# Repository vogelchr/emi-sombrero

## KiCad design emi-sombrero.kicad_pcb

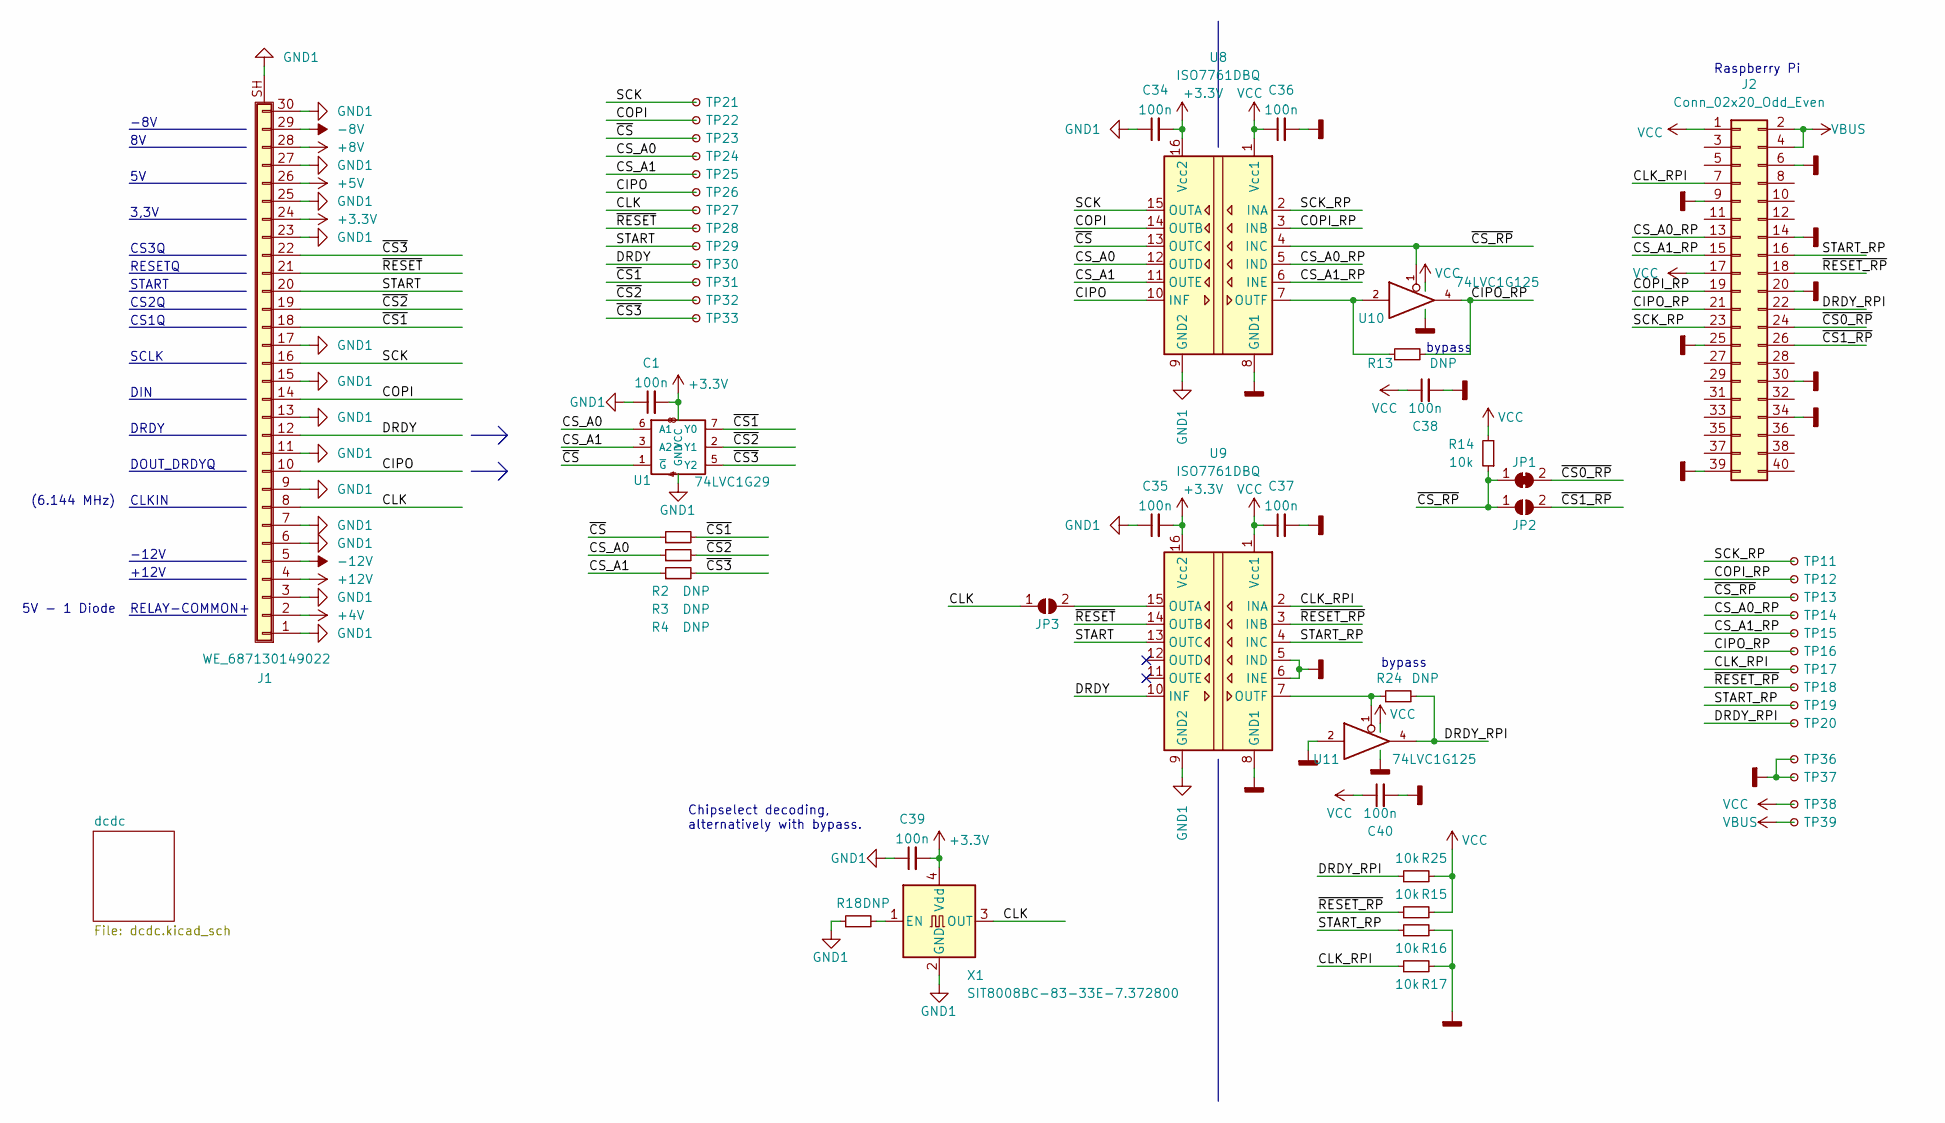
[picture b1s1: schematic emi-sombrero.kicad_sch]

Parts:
C1, C34, C35, C36, C37, C38, C39, C40: 100n; C_0603_1608Metric
J1: WE_687130149022; Hirose_FH12-30S-0.5SH_1x30-1MP_P0.50mm_Horizontal
J2: Conn_02x20_Odd_Even; PinHeader_2x20_P2.54mm_Vertical
JP1: SolderJumper_2_Bridged; SolderJumper-2_P1.3mm_Bridged_Pad1.0x1.5mm
JP2, JP3: SolderJumper_2_Open; SolderJumper-2_P1.3mm_Open_Pad1.0x1.5mm
R2, R3, R4, R13, R18, R24: DNP; R_0603_1608Metric
R14, R15, R16, R17, R25: 10k; R_0603_1608Metric
TP11, TP12, TP13, TP14, TP15, TP16, TP17, TP18, TP19, TP20, TP21, TP22, TP23, TP24, TP25, TP26, TP27, TP28, TP29, TP30, TP31, TP32, TP33, TP36, TP37, TP38, TP39: TestPoint_Small; TestPoint_Pad_1.5x1.5mm
U1: 74LVC1G29; SSOP-8_2.95x2.8mm_P0.65mm
U8, U9: ISO7761DBQ; SSOP-16_3.9x4.9mm_P0.635mm
U10, U11: 74LVC1G125; SOT-23-5
X1: SIT8008BC-83-33E-7.372800; Oscillator_SMD_TXC_7C-4Pin_5.0x3.2mm

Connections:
+3V3: C1.2, C34.2, C35.2, C39.2, J1.24, U1.8 (VCC), U8.16 (Vcc2), U9.16 (Vcc2), X1.4 (Vdd); also elsewhere on the board
+4V: J1.2; also elsewhere on the board
+5V: J1.26; also elsewhere on the board
+8V: J1.28; also elsewhere on the board
+12V: J1.4; also elsewhere on the board
-8V: J1.29; also elsewhere on the board
-12V: J1.5; also elsewhere on the board
/CIPO: J1.10, TP26.1, U8.10 (INF)
/CIPO_RP: J2.21, R13.2, TP16.1, U10.4
/CLK: J1.8, JP3.1 (A), TP27.1, X1.3 (OUT)
/CLK_RPI: J2.7, R17.1, TP17.1, U9.2 (INA)
/COPI: J1.14, TP22.1, U8.14 (OUTB)
/COPI_RP: J2.19, TP12.1, U8.3 (INB)
/CS_A0: R3.1, TP24.1, U1.6 (A1), U8.12 (OUTD)
/CS_A0_RP: J2.13, TP14.1, U8.5 (IND)
/CS_A1: R4.1, TP25.1, U1.3 (A2), U8.11 (OUTE)
/CS_A1_RP: J2.15, TP15.1, U8.6 (INE)
/DRDY: J1.12, TP30.1, U9.10 (INF)
/DRDY_RPI: J2.22, R24.2, R25.1, TP20.1, U11.4
/SCK: J1.16, TP21.1, U8.15 (OUTA)
/SCK_RP: J2.23, TP11.1, U8.2 (INA)
/START: J1.20, TP29.1, U9.13 (OUTC)
/START_RP: J2.16, R16.1, TP19.1, U9.4 (INC)
/~CS0_RP: J2.24, JP1.2 (B)
/~CS1_RP: J2.26, JP2.2 (B)
/~CS1: J1.18, R2.2, TP31.1, U1.7 (Y0)
/~CS2: J1.19, R3.2, TP32.1, U1.2 (Y1)
/~CS3: J1.22, R4.2, TP33.1, U1.5 (Y2)
/~CS_RP: JP1.1 (A), JP2.1 (A), R14.1, TP13.1, U8.4 (INC), U10.1
/~CS: R2.1, TP23.1, U1.1 (~G), U8.13 (OUTC)
/~RESET_RP: J2.18, R15.1, TP18.1, U9.3 (INB)
/~RESET: J1.21, TP28.1, U9.14 (OUTB)
GND: C36.2, C37.2, C38.2, C40.2, J2.6, J2.9, J2.14, J2.20, J2.25, J2.30, J2.34, J2.39, R16.2, R17.2, TP36.1, TP37.1, U8.8 (GND1), U9.5 (IND), U9.6 (INE), U9.8 (GND1), U10.3 (GND), U11.2, U11.3 (GND); also elsewhere on the board
GND1: C1.1, C34.1, C35.1, C39.1, J1.1, J1.3, J1.6, J1.7, J1.9, J1.11, J1.13, J1.15, J1.17, J1.23, J1.25, J1.27, J1.30, J1.SH (Shield), R18.1, U1.4 (GND), U8.9 (GND2), U9.9 (GND2), X1.2 (GND); also elsewhere on the board
unnamed: JP3.2 (B), U9.15 (OUTA)
unnamed: R13.1, U8.7 (OUTF), U10.2
unnamed: R18.2, X1.1 (EN)
unnamed: R24.1, U9.7 (OUTF), U11.1
VBUS: J2.2, J2.4, TP39.1; also elsewhere on the board
VCC: C36.1, C37.1, C38.1, C40.1, J2.1, J2.17, R14.2, R15.2, R25.2, TP38.1, U8.1 (Vcc1), U9.1 (Vcc1), U10.5 (VCC), U11.5 (VCC); also elsewhere on the board

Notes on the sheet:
CLKIN
bypass
3,3V
DIN
(6.144 MHz)
-12V
RELAY-COMMON+
DRDY
Raspberry Pi
-8V
CS1Q
Chipselect decoding, alternatively with bypass.
START
CS3Q
RESETQ
SCLK
DOUT_DRDYQ
+12V
CS2Q
5V - 1 Diode

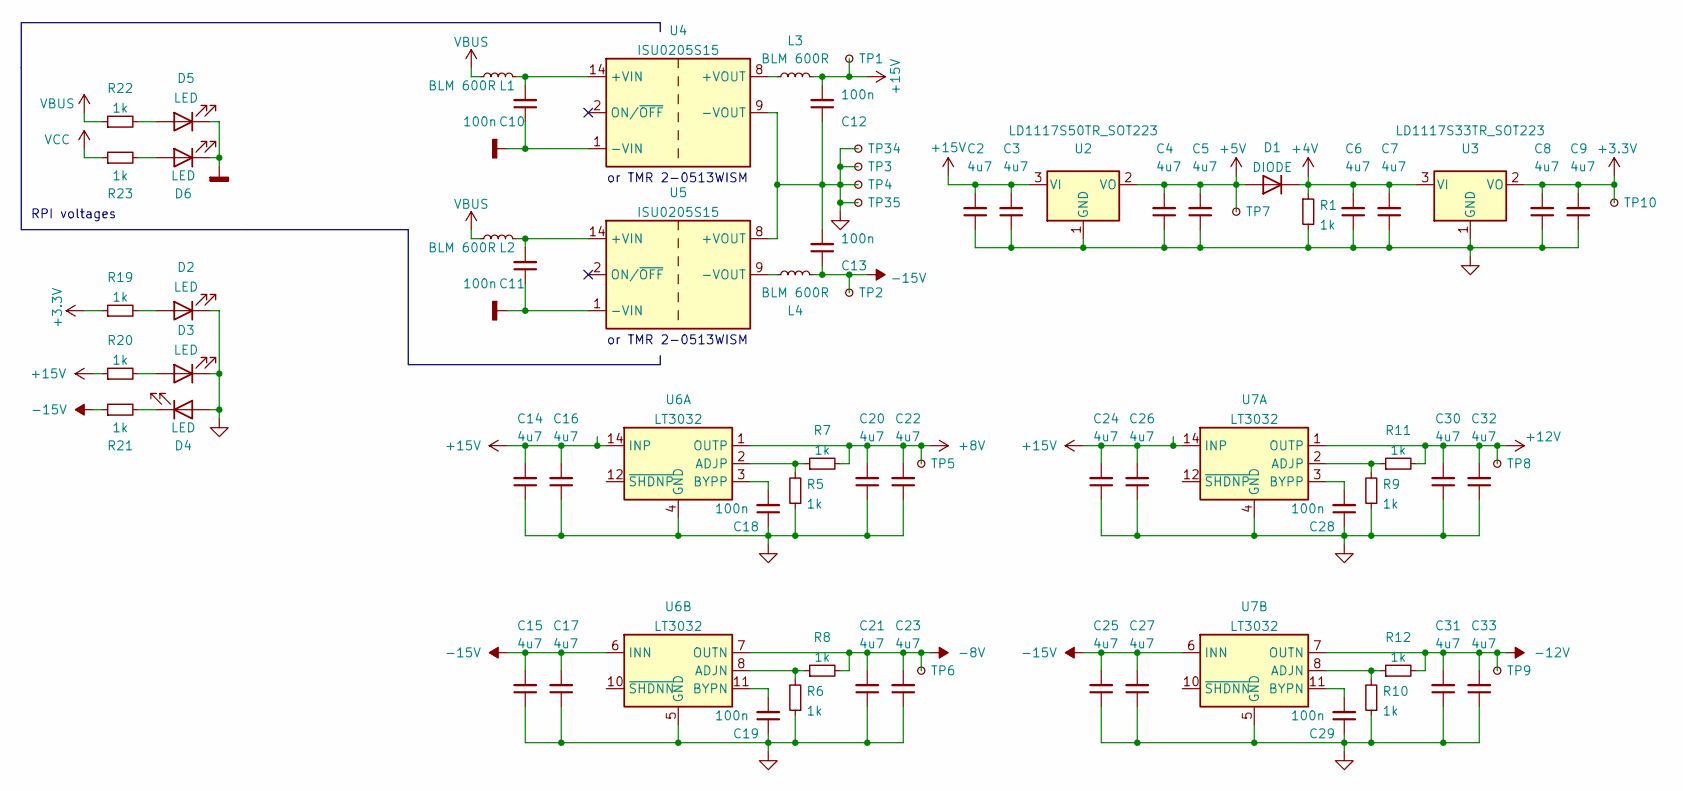
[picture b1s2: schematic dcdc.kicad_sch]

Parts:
C2, C3, C4, C5, C6, C7, C8, C9, C14, C15, C16, C17, C20, C21, C22, C23, C24, C25, C26, C27, C30, C31, C32, C33: 4u7; C_0603_1608Metric
C10, C11, C12, C13, C18, C19, C28, C29: 100n; C_0603_1608Metric
D1: DIODE; D_MELF
D2, D3, D4, D5, D6: LED; LED_0603_1608Metric
L1, L2, L3, L4: BLM 600R; L_0603_1608Metric
R1, R5, R6, R7, R8, R9, R10, R11, R12, R19, R20, R21, R22, R23: 1k; R_0603_1608Metric
TP1, TP2, TP3, TP4, TP5, TP6, TP7, TP8, TP9, TP10, TP34, TP35: TestPoint_Small; TestPoint_Pad_1.5x1.5mm
U2: LD1117S50TR_SOT223; SOT-223-3_TabPin2
U3: LD1117S33TR_SOT223; SOT-223-3_TabPin2
U4, U5: ISU0205S15; Converter_DCDC_XP_POWER-ISU02_SMD
U6, U7: LT3032; Linear_DE14MA

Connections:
+3V3: C8.2, C9.2, R19.1, TP10.1, U3.2 (VO); also elsewhere on the board
+4V: C6.2, C7.2, D1.2 (K), R1.1, U3.3 (VI); also elsewhere on the board
+5V: C4.2, C5.2, D1.1 (A), TP7.1, U2.2 (VO); also elsewhere on the board
+8V: C20.2, C22.2, R7.2, TP5.1, U6.1 (OUTP); also elsewhere on the board
+12V: C30.2, C32.2, R11.2, TP8.1, U7.1 (OUTP); also elsewhere on the board
+15V: C2.2, C3.2, C12.2, C14.2, C16.2, C24.2, C26.2, L3.2, R20.1, TP1.1, U2.3 (VI), U6.14 (INP), U7.14 (INP)
-8V: C21.2, C23.2, R8.2, TP6.1, U6.7 (OUTN); also elsewhere on the board
-12V: C31.2, C33.2, R12.2, TP9.1, U7.7 (OUTN); also elsewhere on the board
-15V: C13.1, C15.2, C17.2, C25.2, C27.2, L4.2, R21.1, TP2.1, U6.6 (INN), U6.9 (INN), U7.6 (INN), U7.9 (INN)
GND: C10.1, C11.1, D5.1 (K), D6.1 (K), U4.1 (-VIN), U5.1 (-VIN); also elsewhere on the board
GND1: C2.1, C3.1, C4.1, C5.1, C6.1, C7.1, C8.1, C9.1, C12.1, C13.2, C14.1, C15.1, C16.1, C17.1, C18.1, C19.1, C20.1, C21.1, C22.1, C23.1, C24.1, C25.1, C26.1, C27.1, C28.1, C29.1, C30.1, C31.1, C32.1, C33.1, D2.1 (K), D3.1 (K), D4.2 (A), R1.2, R5.1, R6.1, R9.1, R10.1, TP3.1, TP4.1, TP34.1, TP35.1, U2.1 (GND), U3.1 (GND), U4.9 (-VOUT), U5.8 (+VOUT), U6.4 (GND), U6.5 (GND), U7.4 (GND), U7.5 (GND); also elsewhere on the board
unnamed: C10.2, L1.2, U4.14 (+VIN)
unnamed: C11.2, L2.2, U5.14 (+VIN)
unnamed: C18.2, U6.3 (BYPP)
unnamed: C19.2, U6.11 (BYPN)
unnamed: C28.2, U7.3 (BYPP)
unnamed: C29.2, U7.11 (BYPN)
unnamed: D2.2 (A), R19.2
unnamed: D3.2 (A), R20.2
unnamed: D4.1 (K), R21.2
unnamed: D5.2 (A), R22.2
unnamed: D6.2 (A), R23.2
unnamed: L3.1, U4.8 (+VOUT)
unnamed: L4.1, U5.9 (-VOUT)
unnamed: R5.2, R7.1, U6.2 (ADJP)
unnamed: R6.2, R8.1, U6.8 (ADJN)
unnamed: R10.2, R12.1, U7.8 (ADJN)
unnamed: R9.2, R11.1, U7.2 (ADJP)
VBUS: L1.1, L2.1, R22.1; also elsewhere on the board
VCC: R23.1; also elsewhere on the board

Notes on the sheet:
RPI voltages
or TMR 2-0513WISM

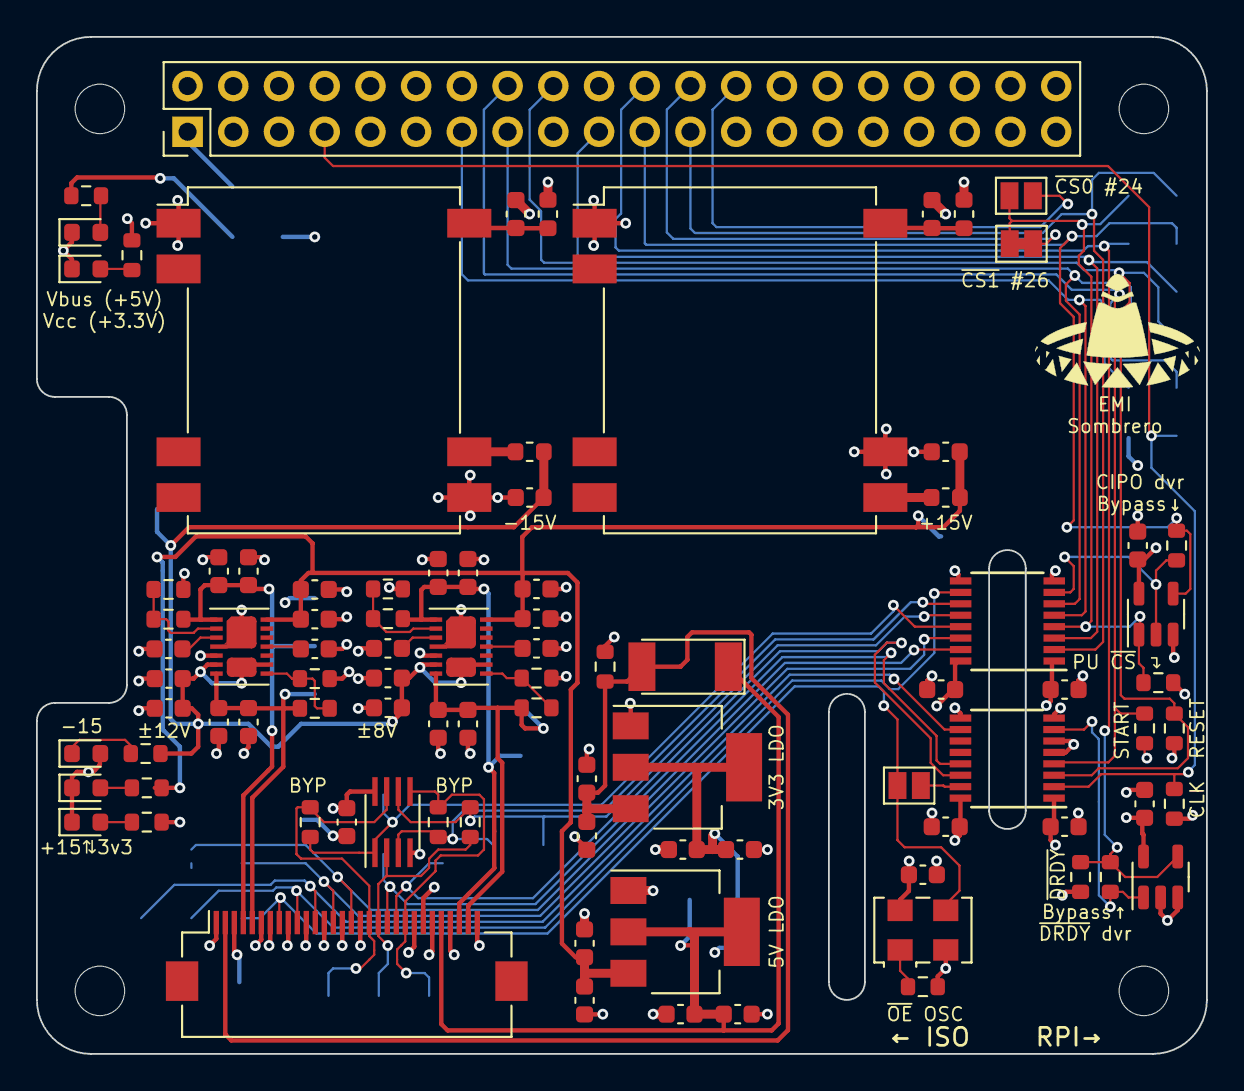
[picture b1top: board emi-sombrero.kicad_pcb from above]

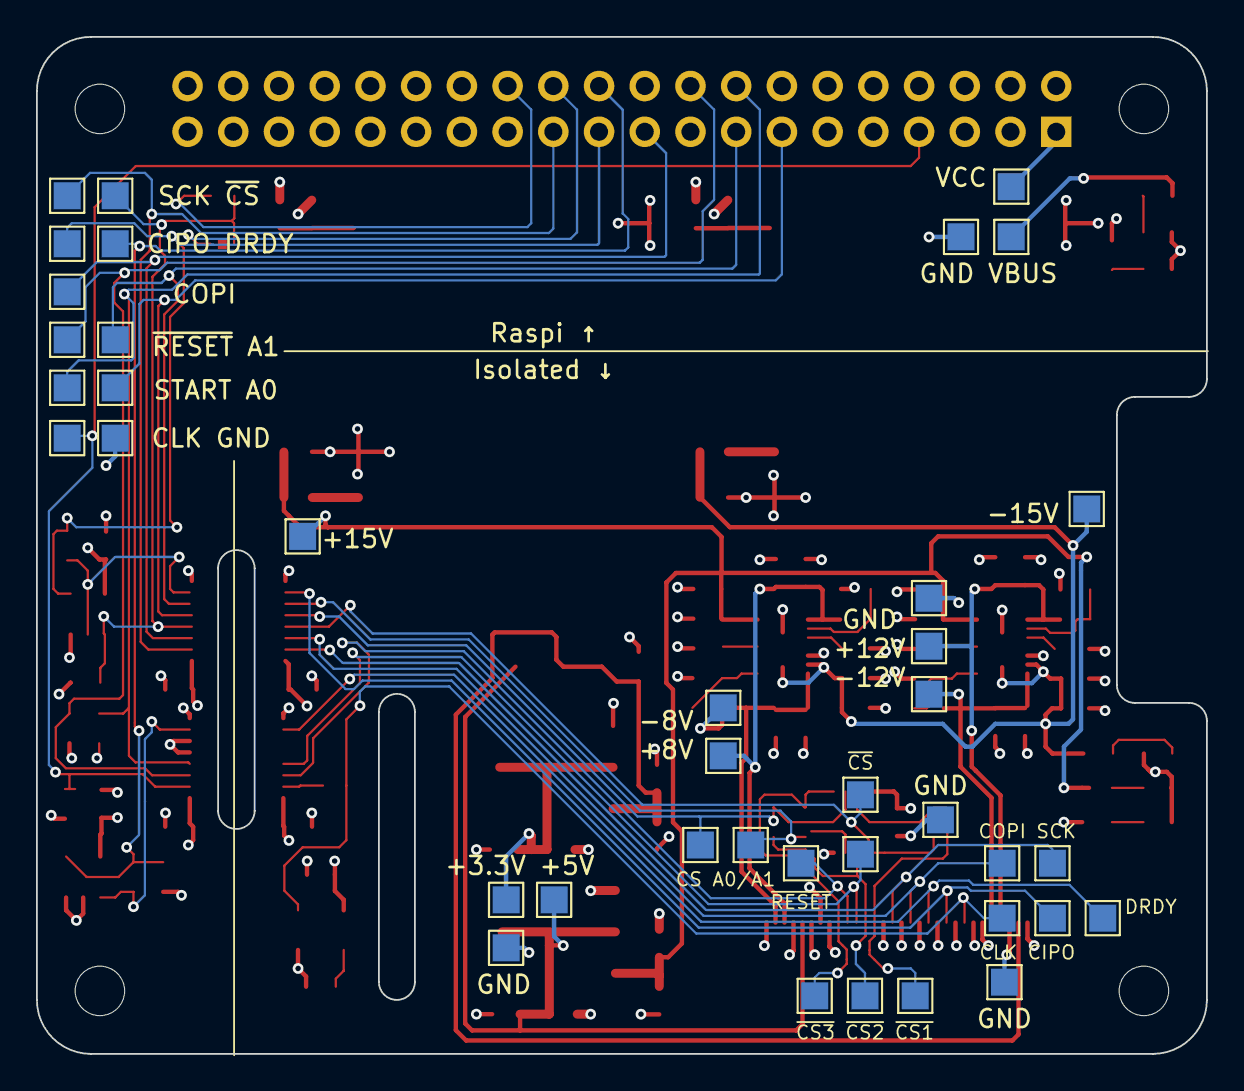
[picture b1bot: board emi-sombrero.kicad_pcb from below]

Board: 4 copper layers, 65.0 x 56.5 mm, 131 parts (39 on the bottom side), 59 nets.

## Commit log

2021-11-28 Initially empty repository.
2021-11-28 Initial checkin.
2021-11-28 Add more testpoints, make DRDY optionally open collector.
